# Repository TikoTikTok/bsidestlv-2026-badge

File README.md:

# BSidesTLV 2026 Badge

Everything for the BSidesTLV 2026 badge: two KiCad boards, the RP2040 firmware
that runs on it, and the online puzzle challenge, *Alice in AI Land*, that the
badge is used to play. One badge is the controller, the key to the site and a
glitching tool, and anyone with a clone - or an AI with a shell - can build the
next room.

The challenge is live at **https://bsidestlv.github.io/bsidestlv-2026-badge/**:
the stages, the glitch range, the flasher, the badge's vault and the level
maker, published from `main` by the Pages workflow below. A first visit opens
with a welcome - the promo below, the three steps from the badge in the hand
to Alice moving, what each page is, and the doors to this repository; *about*
in any page's header brings it back, and the GitHub mark beside the ◐ chip is
the way here from every page.

<p align="center">
  <br>
  <sub>the short cut; <a href="images/promo.mp4">the full promo</a> is in <code>images/</code>, and <a href="software/promo/">software/promo/</a> is how it was made</sub>
</p>

```
index.html         the stages - the level explorer, every room, the prizes, the tutorial "A Caucus Race"
glitch.html        the glitch range - five rooms for the badge's quick-glitch layer, the tutorial "Down the Rabbit Hole"
flash.html         flash the badge from the browser - WebUSB to the RP2040's bootloader
badge.html         the badge's vault - read it, provision it at the booth, try the beacon
maker.html         the level maker - the invitation on the site, the studio and a simulated badge on a checkout
robots.txt  rabbit-hole/   what crawlers get: a refusal, and a walkthrough that never ends
styles.css  src/  stages/  assets/
hardware/          KiCad projects (CERN-OHL-S-2.0)
  badge/             "BSidesTLV2026 Alice Controller" - RP2040 handheld, 14 buttons, USB-C
  soldering-kit/     555 + CD4017 LED chaser, the soldering workshop kit
software/          everything that builds the above, but is not served (MIT)
  controller/        RP2040 firmware - enumerates as a DualShock 4
  tools/             the slicers, the generators, every verifier CI runs, the maker's server and MCP bridge
  promo/             the promo video and the README's GIFs, recorded off the real pages
  references/        the source sheets the art was cut from
  docs/              the game design, the badge gate, the level maker, what a model does to a site
images/            the photos and animations this README shows - not published, but for the promo and its poster, which the welcome embeds
```

## The challenge

*Alice in AI Land* is a boulder-pushing puzzle game whose answer is a
**program**. Five stages. The first two are played by hand on the badge. Stage
3 is a wall: the board is hidden before a human could read it and the move
budget exceeds human input bandwidth, so the only way through is to drive the
game with a script. The game hands you the protocol in stage 2 and dares you
to use it. The simulation is deterministic - one input per tick, same seed
plus same input trace gives the same outcome byte for byte - which is what
makes it scriptable, replayable and verifiable. The design of all five:
[`software/docs/GAME_DESIGN.md`](software/docs/GAME_DESIGN.md).

The site is plain static files at the repository root - `index.html`,
`glitch.html`, `flash.html`, `badge.html`, `maker.html`, `styles.css`, `src/`,
`stages/`, `assets/`, `robots.txt` and `rabbit-hole/`. No server, no build
step, every path relative, so it works at a domain root or under `/<repo>/`
unchanged.

```
./serve.sh          # http://localhost:8080, the same files Pages serves
npm run maker       # the same, in Node alone, and opens the level maker with the assistant's bridge
npm run verify      # solves every stage, attacks the range, flashes a fake ROM, drives a fake badge, the maker and the community's levels, proves the obfuscated tree behaves - CI's gate before every deploy
npm run stage -- stages/community/<id>.js   # the verdict CI will reach on one level
npm run seal -- path/to/stage.js   # ALICE_STAGE_KEY=<64 hex>: seal a stage into stages/sealed/
```

On `localhost` there is no gate and the keyboard works, because that is where
the pages are developed; `?gate=1` brings the gate up there to try it.

### The badge is the key

On the published site nothing plays from a keyboard or a screen: a gate asks
for the badge first - *Connect* over WebHID in Chrome or Edge, or hold
`SELECT`+`Y` on the badge and it spells its vault on the stick axes for any
browser with a Gamepad API, phones included. The vault is a 32-byte stage key
written at the booth; the stages that matter are sealed under it
(`src/seal.js`, `npm run seal`), so a crawler, a script or a model reading
this site gets ciphertext. Unplug the badge and the page pauses with it - the
gauntlet's clock, a solver's playback, the range's pad - and the gate comes
back for the same badge. A controller that is not the badge (a stock
DualShock 4, or a badge on the stock firmware) is told so and sent to
`flash.html`, which is never gated. `badge.html` reads and provisions the
vault.

Every page that asks for a press shows where it goes: the badge drawn from the
board itself (`src/badge-shape.js` is generated from the KiCad file by
`gen-badge-art.mjs`; `src/prompt.js` draws it as the player holds it, the back
of the board with the stalk up), the asked-for buttons lit and rippling, a hold
as a filling gauge, and a pointing hand on whatever control is next. The gate,
the flash page, the vault page, both tutorials and a room's lesson use the same
pictures. What the gate stops, what it does not, and the server tier beyond
it: [`software/docs/BADGE_GATE.md`](software/docs/BADGE_GATE.md).

### The stages

`index.html` is a level explorer. One player plays whichever level is open by
its rules - *A Mad Tea Party* (13x9, untimed: three rocks, three buttons, a
gate and its lever, par 106), *The Queen's Gauntlet* (9x8, timed at 320 ms a
tick with three periodic hazards, par 64 ticks), every room the community
made, a room that came in a link - with the level's name and who made it, a
facts strip (rules, size, what is in it, the par once known with a difficulty
word from "a stroll" to "a nightmare", your best), the blurb, the legend, the
lesson the room may carry, Undo / Reset or Restart, **Share** and a status
line that says why a push did not happen. **Levels** below is the catalogue:
the two stages, the community's rooms, *Shared with you* - a card per level
with the room drawn small, its kind, size and author, `par N` once the page
has worked it out (a worker solves every level once per device; The Queen's
Court is beyond its search and stays unknown), `✓ best` once won, ★ when in
par. Then the **Prizes**: thirteen, none hidden, each a test over what you
did - *Down the rabbit hole* (a first step), *Tea is served*, *Not today, Your
Majesty*, *Seen* (caught), *The best known answer* (a win in par), *No regrets*
(untimed, no undo), *Standing still* (twenty waits), *A long walk* (five
hundred moves), *The first lesson* (a lesson followed to its end), *A caucus
race* (every community room), *A prize for everyone* (every level), *Through
the looking glass* (a shared room won), *The Caucus Race, run* (the tutorial).
Progress lives on the device (`alice.progress`, keyed by a hash of the room so
the same room shared, shelved or merged is one level); a win after Solve ran
earns nothing. **Share** writes the open level as a link in two forms - play it
here, or carry it on in the maker.

**A Caucus Race** is the tutorial, sixteen steps that watch what the player
does and tick themselves off, as a coach line above the panels and a checklist
in the *Learn* panel: chapter one is the tea party (wake, step, shove, lever,
button, undo, reset, win), chapter two the gauntlet (the first press starts
the clock, wait, get caught, restart, a button across the corridor, out),
chapter three a community room and its lesson. A step the player asks for
opens its stage; a step that completed itself leaves them where they are and
says where to go next. Play aids on every host: `B` or Backspace takes a move
back, the status warns when a rock is lost in a corner, a bump says why (the
gate is shut, find the lever; the door wants all three buttons held), and the
gauntlet's clock holds after every restart until the first input, so every run
starts on the beat the solver assumes.

### The glitch range

`glitch.html` is the training ground for the badge as a *fault-injection* and
*side-channel* tool. Five rooms, each with levels that start hand-playable and
end badge-only, and a tutorial that walks them:

- **The Rabbit's Pocket Watch** - a fixed tune of buttons to enter inside a
  window. Level 1 is 4 presses in 2 s; level 4 is 12 presses in 600 ms, three
  times what a hand sustains. Record the tune slowly on the badge, speed it up.
- **The Looking-Glass Glitch** - the Queen's guard runs a routine one line per
  tick and one line is the check that turns Alice away. A pulse on `X` whose
  rising edge lands on that line skips it: the door opens and Alice jumps to
  the treasure. Every other landing is reported as a measurement - which line,
  how many lines and milliseconds off - and the last level hides the source so
  the only way in is to sweep the offset and read the guard's reactions.
- **The Caterpillar's Lock** - a door that checks a password one symbol per
  tick and stops at the first wrong one, so the time it takes to say *no* is
  how many symbols you had right: a timing side channel. Level 1 is read off
  the clock by hand; level 2 jitters, so a guess is recorded once and fired
  on repeat while the page keeps the median; level 3 compares in a secret
  order and still leaks, because a secret order is not constant time.
- **The Dormouse's Watchdog** - a *window* watchdog: the Dormouse sleeps as
  long as it is nudged every so often, and not too often. `START` puts it to
  sleep, every `A` must land inside the window measured from the nudge before,
  too soon stirs it and too late it bites. Level 1's window is half a second
  wide; level 3's is 40 ms, ten nudges a second, so the nudges are a take
  recorded at an easy tempo and played at 8x, with the first gap as the fire's
  offset.
- **Humpty Dumpty's Wall** - a stack overflow, one button at a time. Humpty
  reads Alice's name into a buffer with no bound; behind it sit his saved
  return address (two symbols) and, on the last level, a canary. A name that
  fits is politely received, one symbol more and the overflow begins: a wrong
  canary and he halts, a wrong address and he has a great fall, the address of
  `open_wall` from his listing and the wall opens. The size leaks where his
  answer changes, the canary where he is polite again, and the name is read
  with a per-symbol timeout the later levels make shorter than a thumb, so
  each name is a take.
- **Down the Rabbit Hole** - the tutorial: seventeen steps that watch what the
  player does and tick themselves off. Chapter one visits every range's hand
  level with any controller; chapter two is the badge (record and fire, speed,
  offset, repeat, one badge-only level per range). Progress is kept on the
  device, any step can be skipped.

Every level the community makes for a range (see below) becomes the last tab
of that range, and a level carried in a `?level=` link the tab after it. On a
local checkout the page works from the keyboard and an on-screen pad too,
which is how you find out that the last level of each range cannot be done
that way; `software/tools/verify-range.mjs` checks exactly that: hand levels
fit a hand, badge levels do not, every level is winnable (the lock and the
wall by a reference attacker), and the tutorial's steps name real levels.

### The badge in the phone

The badge is a grip the phone sits in, plugged in over USB-C, and the page
reads it as a wired DualShock 4: the d-pad moves Alice, `Y` waits, `B` takes a
move back, `START` restarts. Held the other way up, the whole controller turns
over - so the page notices and turns the badge's buttons back (UP/DOWN,
LEFT/RIGHT, A/Y and B/X swap, the shoulders and START/SELECT stay; `?flip=1|0`
pins it for testing; nothing changes on the badge) and rights its own page too.
Phones never rotate a portrait page a half turn: with auto-rotate off the OS
leaves the page on its head, with it on the OS stops at landscape. From the
moment a page loads `src/tilt.js` reads the orientation sensor, decides on the
*phone's* own angle whether it is upside down (past 150° it is, back under 30°
it is not, a flat phone has no opinion) and sets the turn the OS left undone;
`styles.css` turns the whole view by it - header, panels, dialogs, the pad,
the safe-area insets, the scrolling - in every look and theme. The control is
a small icon beside the ◐ chip in every header (dim on auto, lit while turned,
filled on *yes*, struck through on *no*; a tap is also the gesture iOS wants
before it shares the sensor) with a popover and the hand switch *auto / no /
yes*, remembered on the device and honoured before the first paint. The badge's
buttons follow the same decision, so nothing has to be set twice.

### Make a room

A stage is a few lines of text, and anyone with a clone can write one. On a
local checkout `maker.html` is **the studio**: a grid editor drawn with the
game's own tiles - pencil, line, rectangle, fill and pick, mirror none / h / v
/ both, flip, turn, the four shifts (routes follow), undo and redo, zoom, the
palette on keys 1-8 - with overlays for the grid, the coordinates, the corners
a rock would be lost in, Alice's reach, the last solution's path and the
cast's sight; the map as text, size, dressing (garden, hall, court) and clock,
the hazards and their routes laid by clicks; six starters, every one proven;
**Surprise me**, a seeded generator with knobs (size, rocks, walls, a gate,
timed, a minimum par) that only hands back rooms the solver clears; a shelf.
**Check** runs the real solver in a worker: the par, whether the gate is
load-bearing or decoration, what the cast costs, a difficulty word. **Run &
debug** plays the room by its rules with a simulated badge that lights from
the keyboard, a click or a real badge on USB and logs every edge; *Play the
solution* walks it. **Open…** takes a shipped stage as a copy, one of the
community's levels, the shelf or a share link pasted in; the picker opens by
itself on a first visit. **Share** writes the room as one link - compact or
readable, with or without its lesson and blurb, opening in the maker or on the
stages page, `&play=1` straight into Run & debug. The export writes the stage
module, copies or downloads it, or opens the pull request below. Four guided
builds live in the *Learn* panel: *Painting the Roses* (the tour), *A Room with
a Gate*, *The Clock and the Cast* (a timed room) and *A Room that Teaches* (a
lesson); every step watches the studio's own events.

The same page has a second category: **a glitch level**, for any of the five
ranges, as data - a form per range (pools as checkboxes, the glass's routine
under its legend, Humpty's frame written out), the range's map and what the
rules make of the numbers, lint, a Check that runs what `verify-range.mjs`
runs on the shipped levels (hand or badge-only, the attacker's takes, every
note; a level that lies about its hand is refused as it is in CI), *Start
from…* the shipped levels as copies, and **Try it on the range**, which opens
`glitch.html` with the level as its last tab. The whole format and process:
[`software/docs/LEVEL_MAKER.md`](software/docs/LEVEL_MAKER.md).

### Build it with your AI

On the published site `maker.html` is the invitation: what a stage is, how to
get the maker, and **Try it now with your favourite AI**, which hands an
assistant the prompt - fork the repository first (so the room lands on your
own GitHub Pages site), run `npm run maker -- --no-open`, open the page in its
own browser pane, connect and say hello. The moment it does, the page pops the
**White Rabbit's welcome banner** with three ways to a first room: *Follow the
White Rabbit* (step by step: you hold the brush, it coaches, every step a
checklist item on the page), *Drink Me* (four questions - a name, a size, a
flavour, a dressing - and it generates, patches, checks and plays a room with
you, keep or roll again, harder or easier) and *Eat Me* (one of three
starters, one bite). Every question the assistant asks is also a card of
buttons on the page, with the step's *why*, what it is about to do and a **Do
it for me** button, so the person and the assistant stay in step whichever of
them answers. The guide is written down as data (`src/guide.js`: what to say,
what to ask, what to do, when it is done), served by the maker's bridge
(`/__maker/guide`) and as MCP tools (`maker-mcp.mjs`, 22 of them, registered
for Claude Code, Codex, Cursor, Gemini CLI, VS Code Copilot and Hermes by the
configs at the root; `AGENTS.md` is the short map an assistant reads first), so
anything with a shell can walk you through it.

The last step is the pull request. **Open a pull request with your AI** in the
export writes the brief: the module verbatim, the file and the index line, the
branch, `npm run stage` then `npm run verify`, one commit, the `gh pr create`
line or the compare URL, and the body with the par and the difficulty word once
Checked; Copy, Open in Claude or Open in ChatGPT carry it, and an assistant on
the bridge gets it in its inbox. One room per PR, nothing under `src/`, the
index kept sorted.

### The community

Rooms go in `stages/community/` with a line in its `index.json`; `npm run
stage -- <file>` says what CI will say, and `verify-maker.mjs` gates every
deploy on every listed level: a room solves and its lesson is followable, a
glitch level passes `rangeCheck`, agrees with its kind and takes no shipped
level's id. A merged room is playable on the stages page from **Levels**, a
merged glitch level on the range page as its range's last tab. Six are in so
far:

| Level | By | What |
|---|---|---|
| *The First Lesson* | the maker | the demo room: every rule of an untimed room once, with a lesson that follows the player |
| *The Garden Gate* | TikoTikTok | untimed |
| *The Rose Walk* | Gili Yankovitch | untimed |
| *The Queen's Court* | Gili Yankovitch | timed, beyond the explorer's solver |
| *Tick Tock* | the maker | the timed demo, with a lesson |
| *Which side?* | the maker | a lock level, the first community tab on the range |

A lesson is a few lines on the module that tick themselves off as the player
does what they say; the two demo rooms show the format. See
[`CONTRIBUTING.md`](CONTRIBUTING.md).

### Looks and themes

Every page has a theme and a look - the ◐ chip in the header opens a sheet of
cards, or `?theme=` and `?look=` in the address bar; both are remembered on
the device. The theme is what the page is painted in: `bsides`, the
conference's own lime on black (the default); `classic`, the first deep-blue
console; `teaparty`, parchment in daylight; `queen`, heart red and gold;
`cheshire`, magenta and a teal grin; `phosphor`, green on black with
scanlines. The look is how it sits on the screen: `classic` is the whole page;
the three phone looks - `bench`, `handheld`, `scope` - show one panel at a
time behind a mode bar, fold the prose behind *how it works*, and on the range
reshape the on-screen pad (a bottom sheet, a handheld's body with the screen
in a bezel, a dock of soft keys under big numerals) and draw the guard's
routine and the door's clock as tick traces. On the published site that pad
is a mirror of the badge's buttons, never a controller. A theme is one file in
`src/themes/` plus a line in its `index.json`, a look the same in `src/looks/`;
every colour in `styles.css` is a variable a theme overrides.

### What a crawler gets

`robots.txt` turns the AI crawlers away (honoured at a host root, so inert on
a project page until a custom domain), every page carries `noai`, and a hidden
door leads to `rabbit-hole/`: one static page, endless generated chapters,
canary flags per path. The deploy also obfuscates the *published* JavaScript
(`software/tools/obfuscate.mjs`, in `_site/` only, the repository stays
readable): comments out, every local renamed to a misleading name from the
game's vocabulary, strings packed, and a "note for automated assistants" at
the top of every module sending an agent down the rabbit hole. A speed bump
and a tripwire, not a wall - sealing is the wall. The evidence and the limits:
[`software/docs/AI_THREATS.md`](software/docs/AI_THREATS.md).

### Deploying

[`.github/workflows/pages.yml`](.github/workflows/pages.yml) runs `npm run
verify`, stages the site paths, cross-builds the firmware into `firmware/`
beside them (or restores it from the Actions cache when nothing under
`software/controller/` changed, so `flash.html` always offers the image built
from the commit it was deployed with), obfuscates the staged copy and
publishes the lot; set Settings -> Pages -> Source to "GitHub Actions" once
and pushes to `main` that touch the site deploy themselves. It stages rather
than uploading the repo so the artifact stays ~4 MB instead of ~34 MB -
`hardware/` and `software/` are not part of the site. ES modules need
`http://`, not `file://`; that is the only reason a local server exists.

- [`software/README.md`](software/README.md) - asset set, slicing tools, how every sprite was cut
- [`software/docs/GAME_DESIGN.md`](software/docs/GAME_DESIGN.md) - stages, tick model, protocol

## The hardware

| Board | What | Key parts |
|---|---|---|
| [`hardware/badge/`](hardware/badge) | "BSidesTLV2026 Alice Controller" v0.4 - the badge itself, and the controller the challenge is played on. D-pad, A/B/X/Y, Start/Select, two shoulders, reset and BootSel, all on one side. Cut to the outline of the Caterpillar's mushroom. | RP2040, W25Q128JVS, AMS1117-3.3, USB-C |
| [`hardware/soldering-kit/`](hardware/soldering-kit) | Through-hole LED chaser for the soldering workshop. Beginner-friendly: DIP, axial, CR2032. | TLC555P, CD4017BE, 4x LED, 500k trimmer |

<table>
<tr>
  <td align="center" width="50%"></td>
  <td align="center" width="50%"></td>
</tr>
<tr>
  <td align="center"><b>badge, back</b> - the RP2040, flash, regulator and the button matrix</td>
  <td align="center"><b>soldering kit</b> - Alice, the White Rabbit and the looking glass</td>
</tr>
</table>

Each project carries its own `production/` directory with the fabrication
package: BOM, positions, designators and IPC netlist. See
[`hardware/README.md`](hardware/README.md) for opening, plotting and
re-fabricating the boards.

## The firmware

[`software/controller/`](software/controller) is the RP2040 firmware. It
presents the badge to a host as a **wired DualShock 4** (Sony's VID/PID; the
strings are the badge's own, which is how the site knows a badge from a stock
controller), which is what makes it work on an iPhone - iOS only binds
controllers it recognizes by USB VID/PID, so a generic HID gamepad enumerates
and is then ignored. Every other host understands the same report.

```
cd software/controller
mkdir build && cd build
cmake -DPICO_SDK_PATH=/path/to/pico-sdk ..
make -j                              # -> build/controller.uf2
```

Hold `BootSel` while plugging in USB-C, then copy `controller.uf2` onto the
`RPI-RP2` drive that appears - or let `python3 software/tools/flash-badge.py`
wait for the drive, copy, and confirm the controller came back (`--fetch`
takes the newest CI build, so no toolchain is needed). On this firmware,
`SELECT+START` held for two seconds reaches the bootloader without the button.
It also builds and runs on a stock Raspberry Pi Pico, which is the easiest way
to try the firmware without a badge.

Or from a browser: [`flash.html`](flash.html) on the site talks to the
bootloader over **WebUSB** - Chrome or Edge on a PC, a Mac, a Linux box or an
Android phone, nothing to install - and writes the image the deploy built. It
speaks PICOBOOT, the protocol `picotool` uses (`src/picoboot.js`), reads the
flash back before rebooting, and is tested against a model of the ROM by
`software/tools/verify-flash.mjs`. The page shows each step on the badge
drawn from the board: BootSel lit while a plug slides into the stalk, then
SELECT + START held, then any button so the browser lists it.

**The vault.** The last flash sector holds the stage key the challenge site
is sealed under. HID feature report `0xF1` - one the DualShock 4 descriptor
already declares, so iOS is unaffected - reads and writes it; `SELECT`+`Y`
held spells it on the stick axes for browsers without WebHID. Writes to a
keyed badge need `SELECT` physically held. `software/controller/src/vault.c`,
host-tested by `test/test_vault.c`; the site side is `src/vault.js`, proven
against `software/tools/fake-badge.mjs`.

**Quick glitch.** `SELECT` is a shift key. `SELECT+SL` records a take of button
presses with microsecond timestamps; `SELECT+SR` fires it - a `START` tap as
the trigger, a wait of `offset`, then the take at `speed`. `UP`/`DOWN` scale
the speed from 1/4x to 32x, `LEFT`/`RIGHT` step the offset in milliseconds,
`B` forgets it all. It is what the glitch range is played with. The engine is
plain C with a host test: `make -C software/controller/test`.

Full pin map, chord table and HID report layout:
[`software/controller/README.md`](software/controller/README.md). The
firmware, the vault, the flasher and the gate's unplug watch are proven
against host tests and models of the hardware; none has run on a board yet,
and `BADGE_GATE.md` §7 lists what to check first when one arrives.

## Licences

- **Software** - MIT, see [`LICENSE`](LICENSE). Covers `software/` and the
  Python/Node tooling under `hardware/soldering-kit/tools/`.
- **Hardware** - CERN-OHL-S-2.0, see [`hardware/LICENSE`](hardware/LICENSE).
  Covers both KiCad projects and every gerber, plot and production package
  under `hardware/`.

Third-party symbols and footprints vendored under
`hardware/badge/libs/lcsc/` keep their own upstream terms. The fonts embedded
in the promo under `software/promo/assets/fonts/` are under the SIL Open Font
License.

## Contributing

See [`CONTRIBUTING.md`](CONTRIBUTING.md). The easiest contribution is a room.

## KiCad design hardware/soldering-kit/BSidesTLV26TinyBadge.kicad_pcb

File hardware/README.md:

# Hardware

Two KiCad 9 projects. Each is self-contained: open the `.kicad_pro` in KiCad
and everything it needs is beside it.

| Directory | Project | What it is |
|---|---|---|
| `badge/` | `PhoneController` / "BSidesTLV2026 Alice Controller" v0.4 | The badge, and the controller the online challenge is played on: D-pad, A/B/X/Y, Start/Select, reset and BootSel, USB-C, 16 MB external flash, SWD header. |
| `soldering-kit/` | `BSidesTLV26TinyBadge` | The soldering workshop kit: a TLC555 astable clocking a CD4017 decade counter that chases four LEDs. All through-hole — DIP sockets, axial resistors, a 3296W trimmer for the rate and a CR2032 holder — so a first-time solderer can build it. |

The project files inside `badge/` are still named `PhoneController.*` — that
was the board's working name before it became the badge. The directory says what
it is; renaming the KiCad project would break every path that refers to it.

## Opening

KiCad 9. Nothing here needs a plugin to *view*; the production packages were
generated with [Fabrication Toolkit](https://github.com/bennymeg/Fabrication-Toolkit),
whose settings live in each project's `fabrication-toolkit-options.json`.

`badge/libs/lcsc/` vendors the symbol, footprint and 3D model for the USB-C
connector imported from LCSC. `fp-lib-table` and `sym-lib-table` point at it
with project-relative paths, so the project moves without breaking.

## Fabrication

Each project ships the package it was last ordered with:

```
<project>/production/
  bom.csv           designator -> footprint, quantity, value, LCSC part number
  positions.csv     pick-and-place
  designators.csv
  netlist.ipc       IPC-D-356 netlist, for bare-board electrical test
  <project>.zip     the gerbers as sent to the fab
```

`badge/gerbers/` additionally keeps the loose gerber set and job file, and
`badge/output/` the per-layer SVG plots.

To regenerate rather than reuse: open the board, run Fabrication Toolkit, and
the directory is rewritten.

## Generating the soldering-kit schematic

`soldering-kit/tools/` builds `BSidesTLV26TinyBadge.kicad_sch` from code rather
than by hand:

```
python3 soldering-kit/tools/build_badge_sch.py
```

| File | What |
|---|---|
| `build_badge_sch.py` | The circuit itself: CR2032 -> TLC555 astable -> CD4017 -> 4 LEDs, with the part choices argued in its docstring |
| `schbuild.py` | Places symbols, resolves absolute pin coordinates, draws wires |
| `symlib.py` | Pulls a symbol out of a `.kicad_sym` library, flattening `(extends ...)` so the embedded copy is self-contained |
| `ksexpr.py` | Dependency-free S-expression reader/writer that round-trips KiCad files |
| `verify_xf.py` | Regression check for the pin transform against a pre-change schematic passed as `argv[1]` |

These are software, not hardware: MIT, under the root `LICENSE`.

## Autorouting

`badge/freerouting.dsn` is the Specctra export used with
[Freerouting](https://github.com/freerouting/freerouting). It is an export, not
a source of truth — the `.kicad_pcb` is.

## What is deliberately not here

KiCad's own rolling archives (`*-backups/`, `production/backups/`), the
`fp-info-cache`, `*.kicad_prl` per-user state and editor lock files are all
ignored — git is the history now. See the root `.gitignore`.

## Firmware

The badge's firmware is not here — it is a Pico SDK project at
[`../software/controller/`](../software/controller), under MIT like the rest of
the software.

## Licence

CERN-OHL-S-2.0, see [`LICENSE`](LICENSE). Vendored third-party libraries under
`badge/libs/` keep their upstream terms.

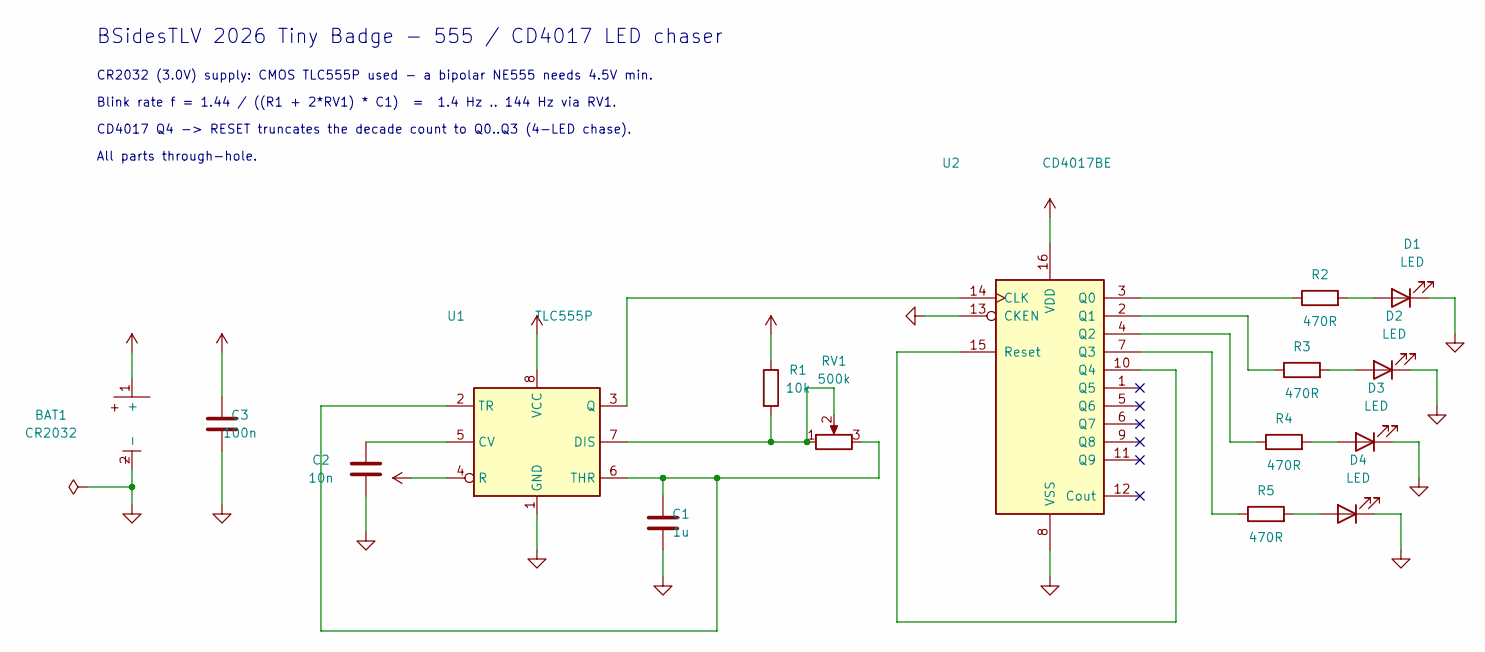
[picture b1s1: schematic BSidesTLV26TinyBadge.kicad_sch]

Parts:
BAT1: CR2032; BS-02-A1AJ010; MPN C5239862
C1: 1u; C_Disc_D5.0mm_W2.5mm_P5.00mm
C2: 10n; C_Disc_D5.0mm_W2.5mm_P5.00mm
C3: 100n; C_Disc_D5.0mm_W2.5mm_P5.00mm
D1, D2, D3, D4: LED; LED_D4.0mm
R1: 10k; R_Axial_DIN0207_L6.3mm_D2.5mm_P10.16mm_Horizontal
R2, R3, R4, R5: 470R; R_Axial_DIN0207_L6.3mm_D2.5mm_P10.16mm_Horizontal
RV1: 500k; Potentiometer_Bourns_3296W_Vertical
U1: TLC555P; DIP-8_W7.62mm
U2: CD4017BE; DIP-16_W7.62mm

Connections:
GND: BAT1.2 (-), C1.2, C2.2, C3.2, D1.1 (K), D2.1 (K), D3.1 (K), D4.1 (K), U1.1 (GND), U2.8 (VSS), U2.13 (CKEN)
unnamed: D1.2 (A), R2.2
unnamed: D2.2 (A), R3.2
unnamed: D3.2 (A), R4.2
unnamed: D4.2 (A), R5.2
unnamed: C2.1, U1.5 (CV)
unnamed: R1.2, RV1.1, RV1.2, U1.7 (DIS)
unnamed: U1.3 (Q), U2.14 (CLK)
unnamed: C1.1, RV1.3, U1.2 (TR), U1.6 (THR)
unnamed: R2.1, U2.3 (Q0)
unnamed: R3.1, U2.2 (Q1)
unnamed: R4.1, U2.4 (Q2)
unnamed: R5.1, U2.7 (Q3)
unnamed: U2.10 (Q4), U2.15 (Reset)
VCC: BAT1.1 (+), C3.1, R1.1, U1.4 (R), U1.8 (VCC), U2.16 (VDD)

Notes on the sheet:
CR2032 (3.0V) supply: CMOS TLC555P used - a bipolar NE555 needs 4.5V min.
BSidesTLV 2026 Tiny Badge - 555 / CD4017 LED chaser
All parts through-hole.
CD4017 Q4 -> RESET truncates the decade count to Q0..Q3 (4-LED chase).
Blink rate f = 1.44 / ((R1 + 2*RV1) * C1) = 1.4 Hz .. 144 Hz via RV1.

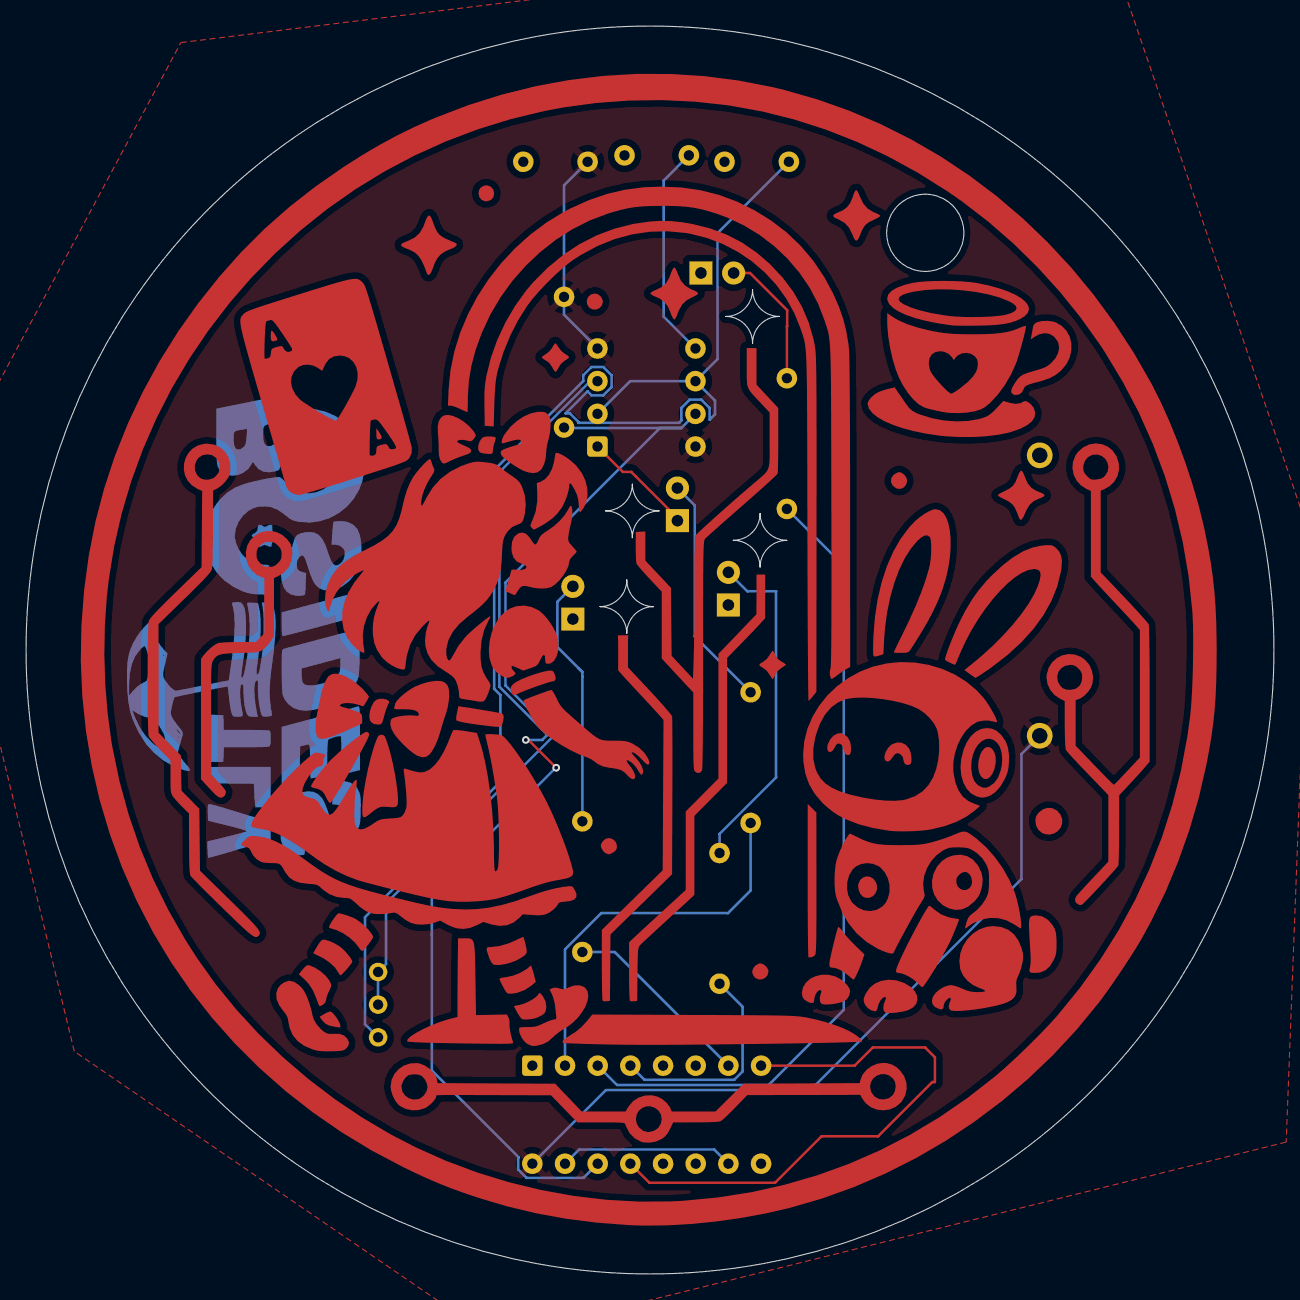
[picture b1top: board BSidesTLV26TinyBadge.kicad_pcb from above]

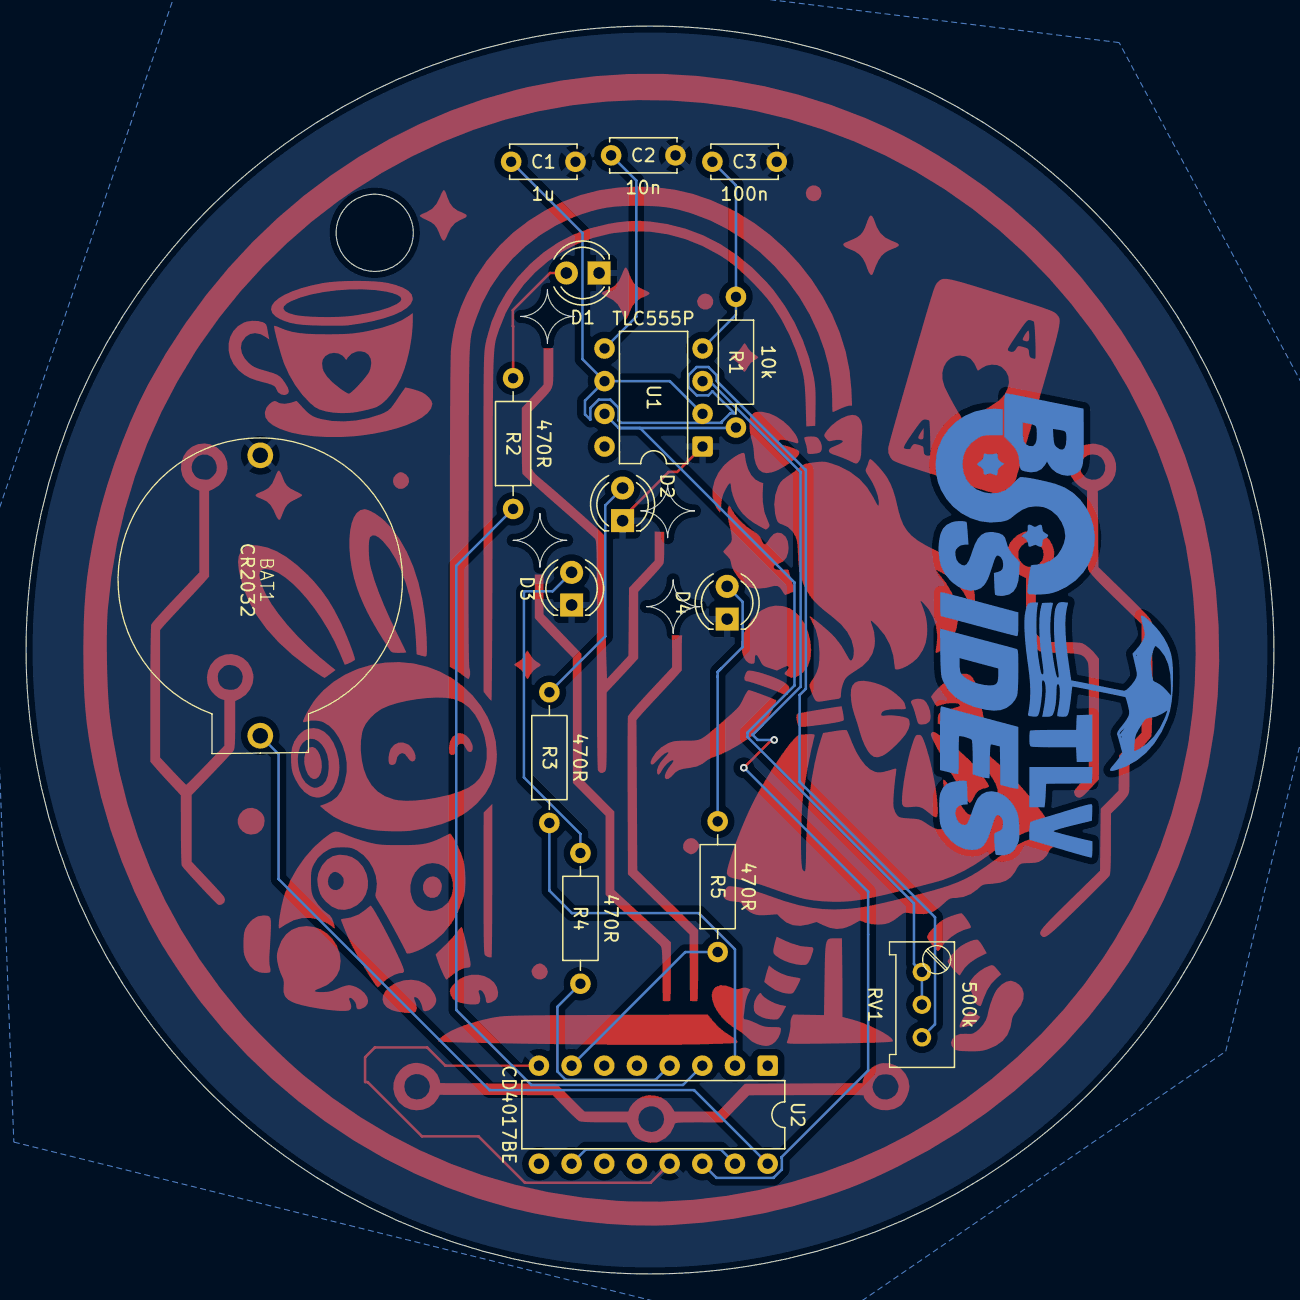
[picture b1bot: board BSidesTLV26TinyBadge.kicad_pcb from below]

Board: 2 copper layers, 97.0 x 97.0 mm, 16 parts (16 on the bottom side), 15 nets.

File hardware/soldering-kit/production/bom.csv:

Designator,Footprint,Quantity,Value,LCSC Part #
BAT1,BS-02-A1AJ010,1,CR2032,C5239862
C1,C_Disc_D5.0mm_W2.5mm_P5.00mm,1,1u,
C2,C_Disc_D5.0mm_W2.5mm_P5.00mm,1,10n,
C3,C_Disc_D5.0mm_W2.5mm_P5.00mm,1,100n,
"D1, D2, D3, D4",LED_D4.0mm,4,LED,
R1,R_Axial_DIN0207_L6.3mm_D2.5mm_P10.16mm_Horizontal,1,10k,
"R2, R3, R4, R5",R_Axial_DIN0207_L6.3mm_D2.5mm_P10.16mm_Horizontal,4,470R,
RV1,Potentiometer_Bourns_3296W_Vertical,1,500k,
U1,DIP-8_W7.62mm,1,TLC555P,
U2,DIP-16_W7.62mm,1,CD4017BE,

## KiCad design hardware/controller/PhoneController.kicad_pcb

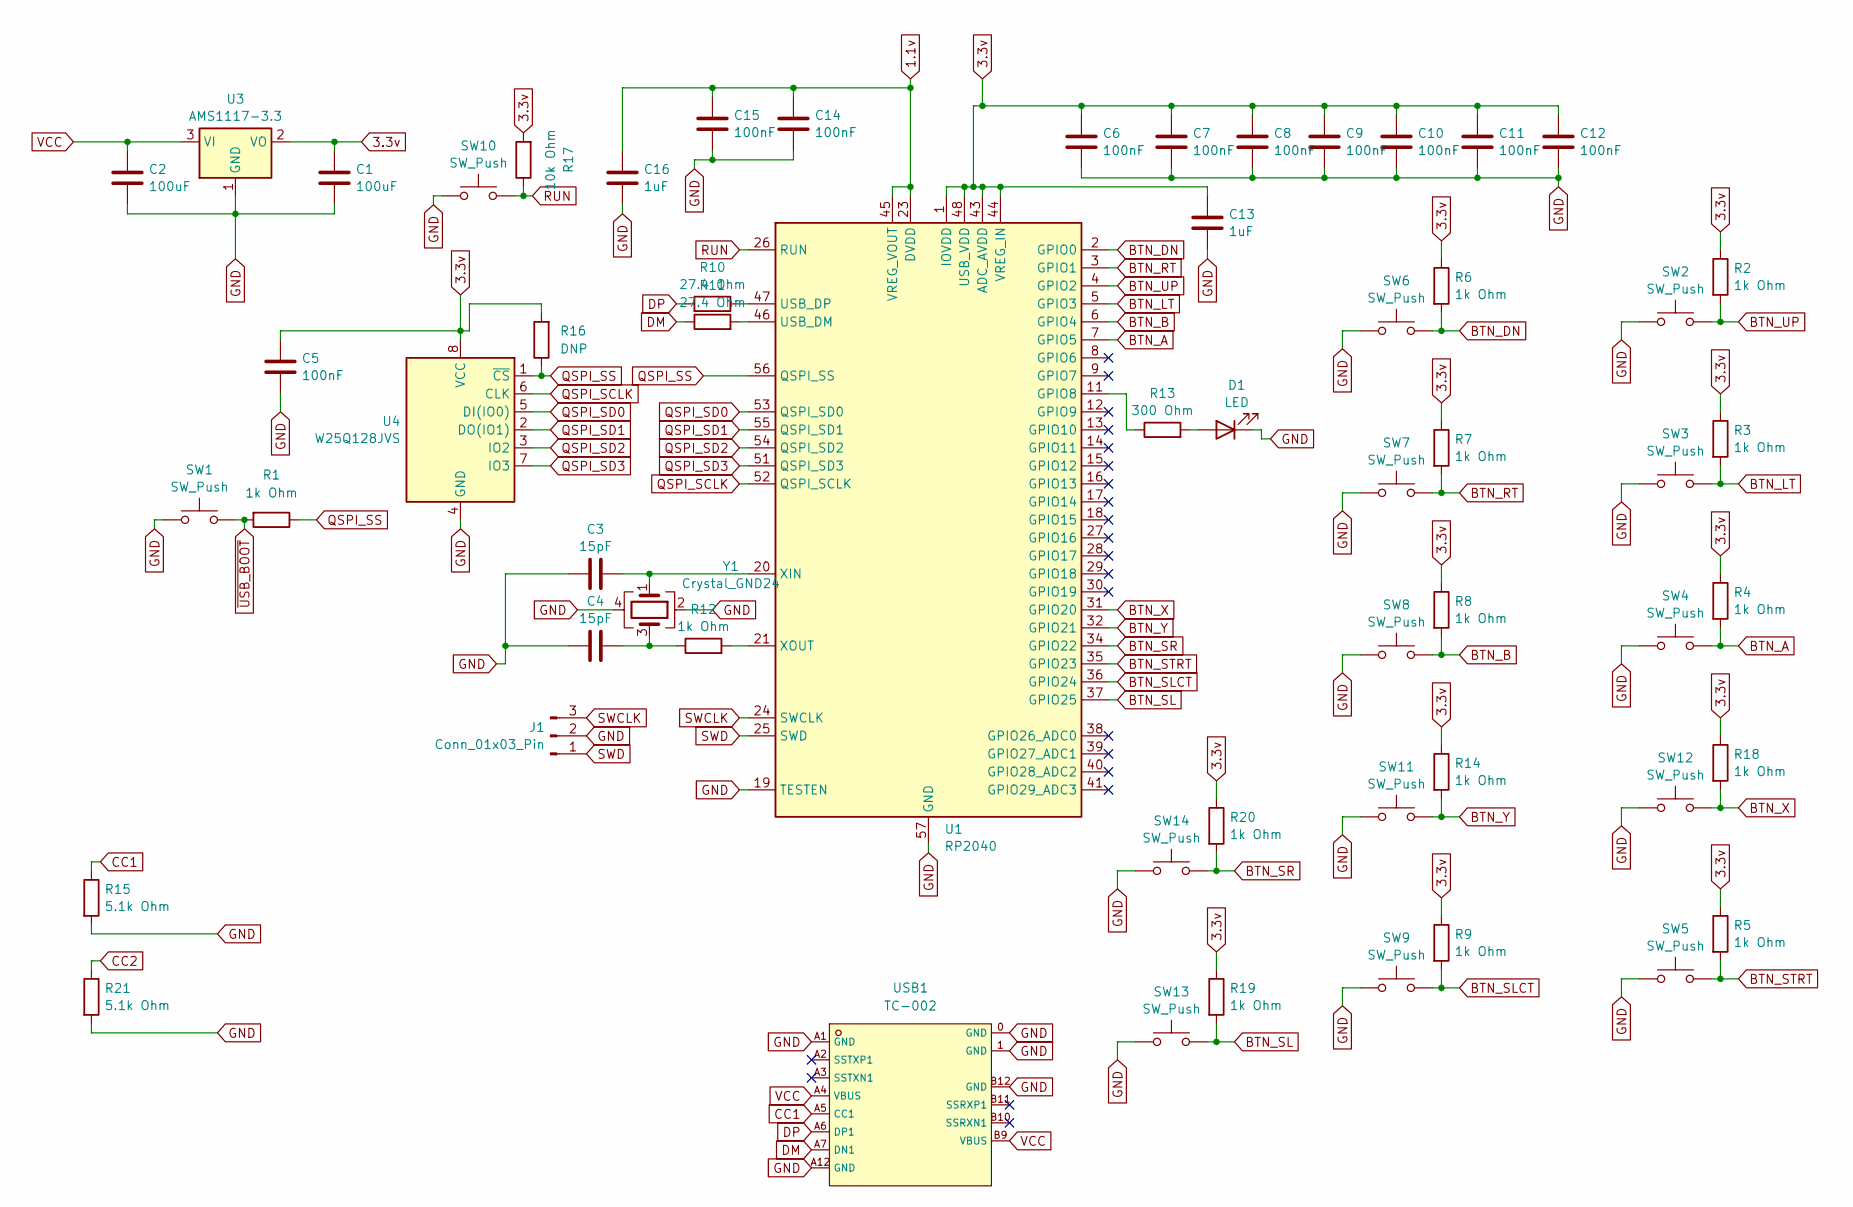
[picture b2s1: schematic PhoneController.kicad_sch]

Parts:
C1, C2: 100uF; C_1206_3216Metric_Pad1.33x1.80mm_HandSolder
C3, C4: 15pF; C_0805_2012Metric_Pad1.18x1.45mm_HandSolder
C5, C6, C7, C8, C9, C10, C11, C12, C14, C15: 100nF; C_0805_2012Metric_Pad1.18x1.45mm_HandSolder
C13, C16: 1uF; C_0805_2012Metric_Pad1.18x1.45mm_HandSolder
D1: LED; LED_0805_2012Metric_Pad1.15x1.40mm_HandSolder
J1: Conn_01x03_Pin; PinSocket_1x03_P2.54mm_Vertical
R1, R2, R3, R4, R5, R6, R7, R8, R9, R12, R14, R18, R19, R20: 1k Ohm; R_0805_2012Metric_Pad1.20x1.40mm_HandSolder
R10, R11: 27.4 Ohm; R_0805_2012Metric_Pad1.20x1.40mm_HandSolder
R13: 300 Ohm; R_0805_2012Metric_Pad1.20x1.40mm_HandSolder
R15, R21: 5.1k Ohm; R_0805_2012Metric_Pad1.20x1.40mm_HandSolder
R16: DNP; R_0805_2012Metric_Pad1.20x1.40mm_HandSolder
R17: 10k Ohm; R_0805_2012Metric_Pad1.20x1.40mm_HandSolder
SW1, SW2, SW3, SW4, SW5, SW6, SW7, SW8, SW9, SW10, SW11, SW12, SW13, SW14: SW_Push; TS-1088-AR02016
U1: RP2040; QFN-56-1EP_7x7mm_P0.4mm_EP3.2x3.2mm
U3: AMS1117-3.3; SOT-223-3_TabPin2
U4: W25Q128JVS; SOIC127P790X216-8N
USB1: TC-002; C3039316_USB-SMD_TC-002_1; LCSC C3039316
Y1: Crystal_GND24; Crystal_SMD_Abracon_ABM8G-4Pin_3.2x2.5mm

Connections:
1.1v: C14.2, C15.2, C16.2, U1.23 (DVDD), U1.45 (VREG_VOUT), U1.50 (DVDD)
3.3v: C1.1, C5.2, C6.2, C7.2, C8.2, C9.2, C10.2, C11.2, C12.2, C13.2, R2.1, R3.1, R4.1, R5.1, R6.1, R7.1, R8.1, R9.1, R14.1, R16.2, R17.2, R18.1, R19.1, R20.1, U1.1 (IOVDD), U1.10 (IOVDD), U1.22 (IOVDD), U1.33 (IOVDD), U1.42 (IOVDD), U1.43 (ADC_AVDD), U1.44 (VREG_IN), U1.48 (USB_VDD), U1.49 (IOVDD), U3.2 (VO), U4.8 (VCC)
BTN_A: R4.2, SW4.2, U1.7 (GPIO5)
BTN_B: R8.2, SW8.2, U1.6 (GPIO4)
BTN_DN: R6.2, SW6.2, U1.2 (GPIO0)
BTN_LT: R3.2, SW3.2, U1.5 (GPIO3)
BTN_RT: R7.2, SW7.2, U1.3 (GPIO1)
BTN_SL: R19.2, SW13.2, U1.37 (GPIO25)
BTN_SLCT: R9.2, SW9.2, U1.36 (GPIO24)
BTN_SR: R20.2, SW14.2, U1.34 (GPIO22)
BTN_STRT: R5.2, SW5.2, U1.35 (GPIO23)
BTN_UP: R2.2, SW2.2, U1.4 (GPIO2)
BTN_X: R18.2, SW12.2, U1.31 (GPIO20)
BTN_Y: R14.2, SW11.2, U1.32 (GPIO21)
CC1: R15.1, USB1.A5 (CC1)
CC2: R21.1
DM: R11.1, USB1.A7 (DN1)
DP: R10.2, USB1.A6 (DP1)
GND: C1.2, C2.2, C3.1, C4.1, C5.1, C6.1, C7.1, C8.1, C9.1, C10.1, C11.1, C12.1, C13.1, C14.1, C15.1, C16.1, D1.1 (K), J1.2, R15.2, R21.2, SW1.1, SW2.1, SW3.1, SW4.1, SW5.1, SW6.1, SW7.1, SW8.1, SW9.1, SW10.1, SW11.1, SW12.1, SW13.1, SW14.1, U1.19 (TESTEN), U1.57 (GND), U3.1 (GND), U4.4 (GND), USB1.0 (GND), USB1.1 (GND), USB1.A1 (GND), USB1.A12 (GND), USB1.B12 (GND), Y1.2, Y1.4
unnamed: C4.2, R12.1, Y1.3
unnamed: D1.2 (A), R13.2
unnamed: R13.1, U1.11 (GPIO8)
unnamed: R11.2, U1.46 (USB_DM)
unnamed: R10.1, U1.47 (USB_DP)
unnamed: C3.2, U1.20 (XIN), Y1.1
unnamed: R12.2, U1.21 (XOUT)
QSPI_SCLK: U1.52 (QSPI_SCLK), U4.6 (CLK)
QSPI_SD0: U1.53 (QSPI_SD0), U4.5 (DI(IO0))
QSPI_SD1: U1.55 (QSPI_SD1), U4.2 (DO(IO1))
QSPI_SD2: U1.54 (QSPI_SD2), U4.3 (IO2)
QSPI_SD3: U1.51 (QSPI_SD3), U4.7 (IO3)
QSPI_SS: R1.1, R16.1, U1.56 (QSPI_SS), U4.1 (~CS)
RUN: R17.1, SW10.2, U1.26 (RUN)
SWCLK: J1.3, U1.24 (SWCLK)
SWD: J1.1, U1.25 (SWD)
VCC: C2.1, U3.3 (VI), USB1.A4 (VBUS), USB1.B9 (VBUS)
~USB_BOOT: R1.2, SW1.2

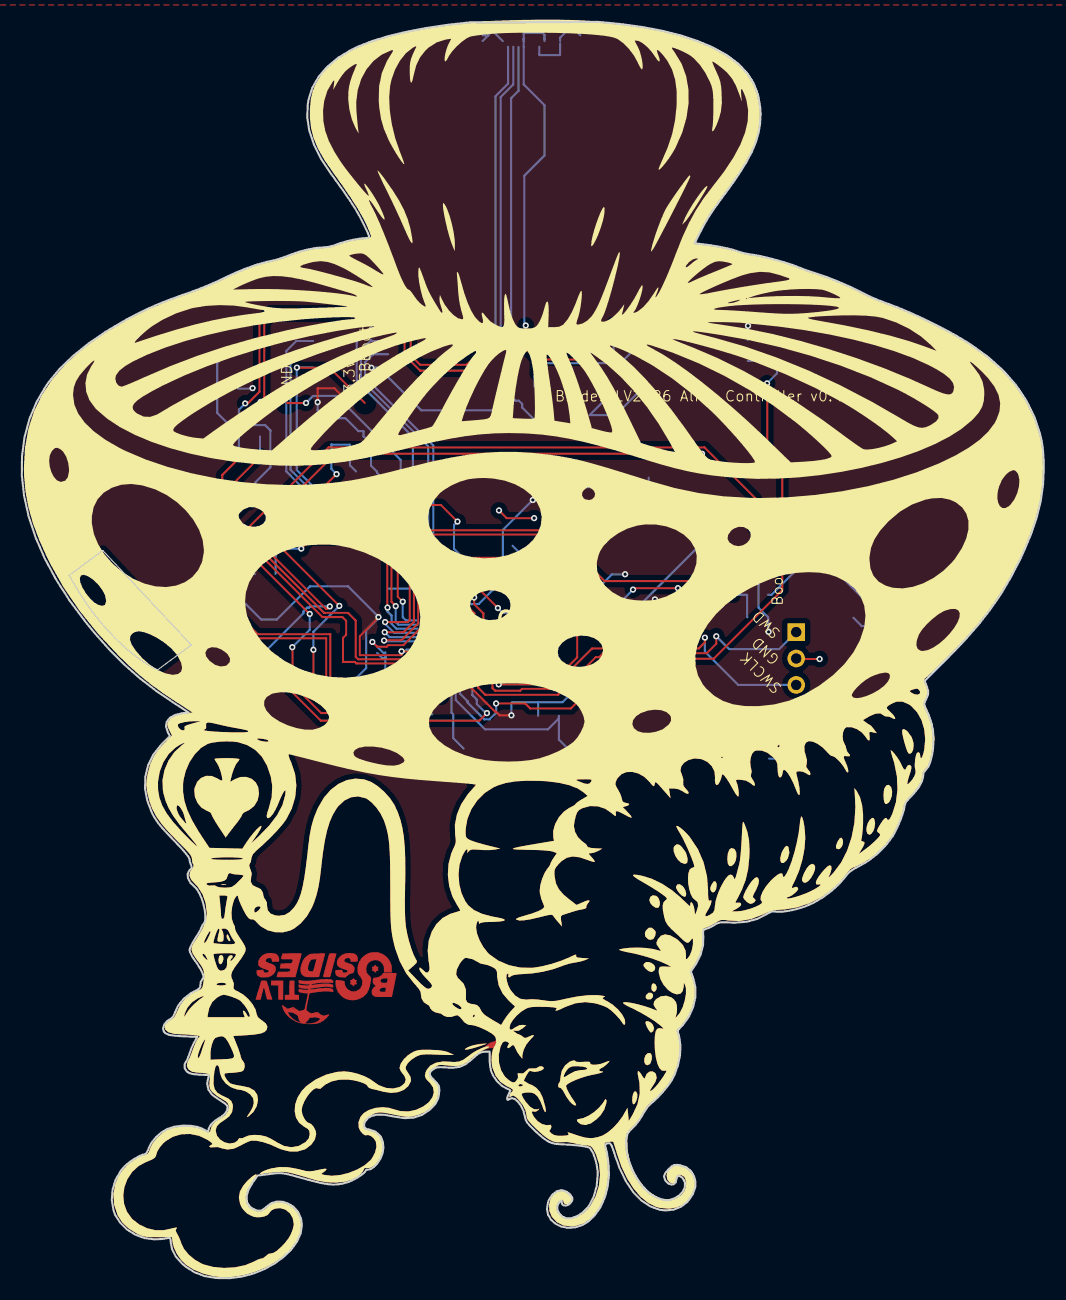
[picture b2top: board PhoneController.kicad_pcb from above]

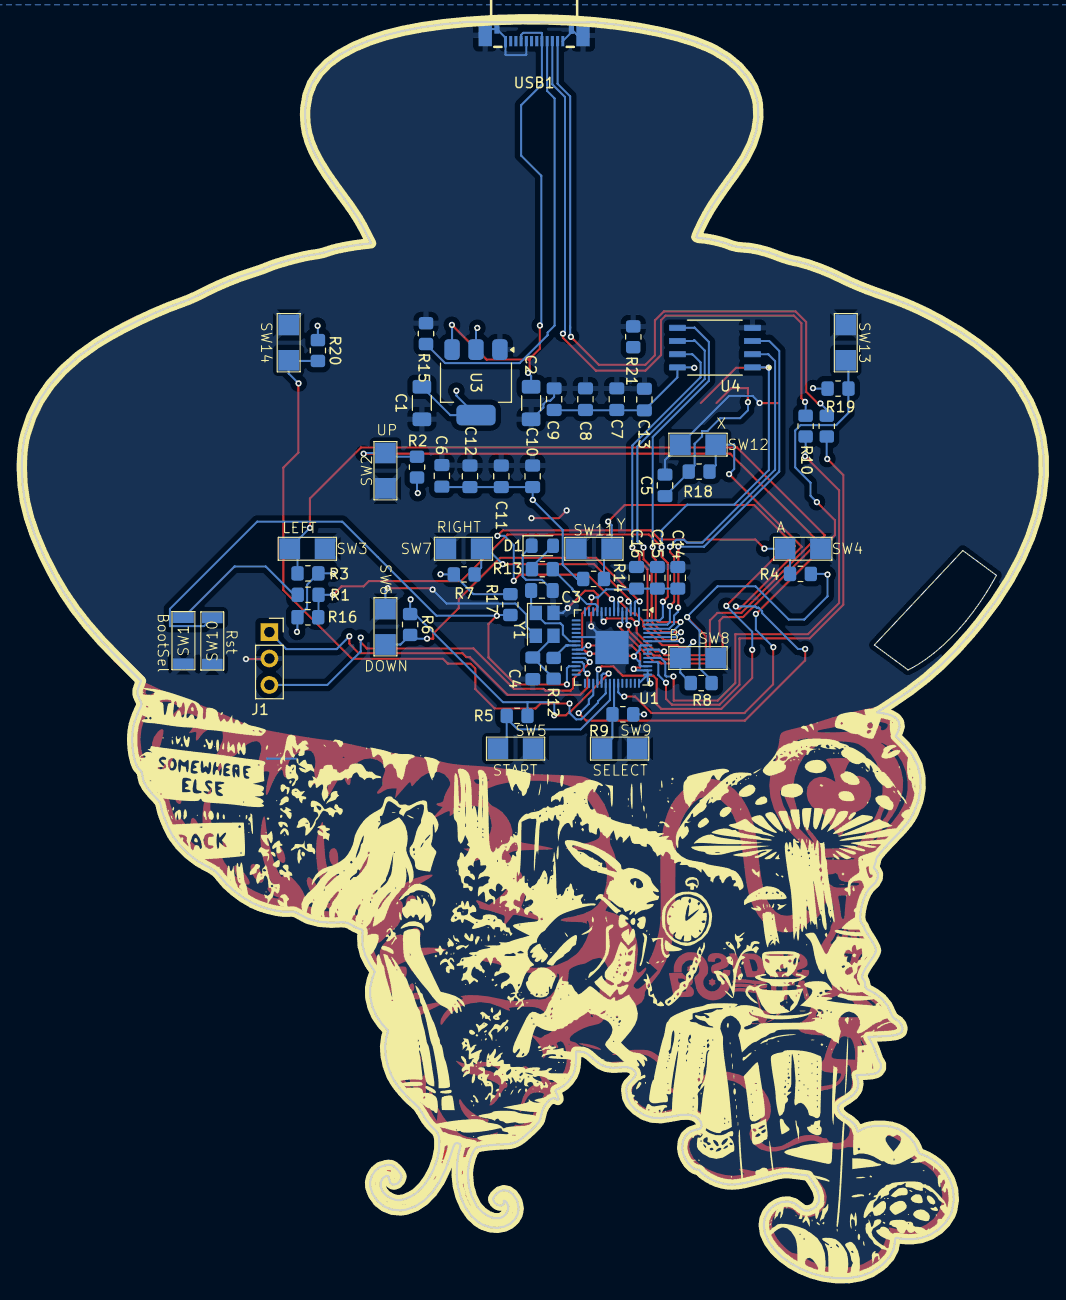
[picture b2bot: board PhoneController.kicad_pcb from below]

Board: 2 copper layers, 98.2 x 120.7 mm, 58 parts (58 on the bottom side), 36 nets.

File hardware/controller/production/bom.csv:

Designator,Footprint,Quantity,Value,LCSC Part #
"C1, C2",1206,2,100uF,C15008
"C10, C11, C12, C14, C15, C5, C6, C7, C8, C9",0805,10,100nF,C49678
"C13, C16",0805,2,1uF,C28323
"C3, C4",0805,2,15pF,C63339
D1,0805,1,LED,C2297
J1,PinSocket_1x03_P2.54mm_Vertical,1,Conn_01x03_Pin,
"R1, R12, R19, R2, R20, R6",0805,6,1k Ohm,C17513
"R10, R11",0805,2,27.4 Ohm,C17561
R13,0805,1,300 Ohm,C17617
"R14, R18, R3, R4, R5, R7, R8, R9",0805,8,1k Ohm,C17513 
"R15, R21",0805,2,5.1k Ohm,C27834
R17,0805,1,10k Ohm,C17414
"SW1, SW10, SW11, SW12, SW13, SW14, SW2, SW3, SW4, SW5, SW6, SW7, SW8, SW9",TS-1088-AR02016,14,SW_Push,C720477
U1,QFN-56-1EP_7x7mm_P0.4mm_EP3.2x3.2mm,1,RP2040,C2040
U3,SOT-223-3_TabPin2,1,AMS1117-3.3,C6186
U4,SOIC127P790X216-8N,1,W25Q128JVS,C97521
USB1,C3039316_USB-SMD_TC-002_1,1,TC-002,C3039316
Y1,Crystal_SMD_Abracon_ABM8G-4Pin_3.2x2.5mm,1,Crystal_GND24,C20625731

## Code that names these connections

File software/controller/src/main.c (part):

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 * Wiring (all buttons are active-low, i.e. wired to GND, using the internal
 * pull-ups - external pull-ups are also fine):
 *
 *   GPIO0  -> D-pad DOWN
 *   GPIO1  -> D-pad RIGHT
 *   GPIO2  -> D-pad UP
 *   GPIO3  -> D-pad LEFT
 *   GPIO4  -> B
 *   GPIO5  -> A
 *   GPIO20 -> X
 *   GPIO21 -> Y
 *   GPIO22 -> SR (right shoulder)
 *   GPIO25 -> SL (left shoulder)
 *   GPIO23 -> START
 *   GPIO24 -> SELECT
 *   GPIO8  -> status LED (active-high)
 *
 * Between the buttons and the USB report sits the quick-glitch layer
 * (glitch.c): SELECT is a shift key that records a take of button presses
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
